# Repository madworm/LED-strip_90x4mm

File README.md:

LED-strip_90.0x3.6mm
=====================

LAYOUT FILES: 90.0mm x 3.6mm LED strip with 9x 0805 LEDs + resistors

---

Before having PC-boards made, please make sure you know about your manufacturer's peculiarities!
Especially drill-sizes and their tolerances may vary too much and give you trouble.

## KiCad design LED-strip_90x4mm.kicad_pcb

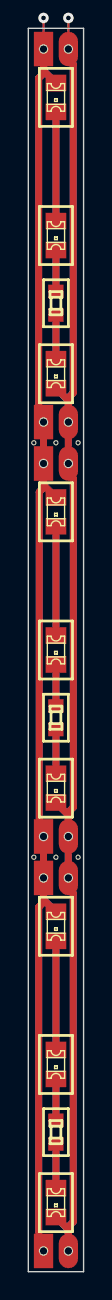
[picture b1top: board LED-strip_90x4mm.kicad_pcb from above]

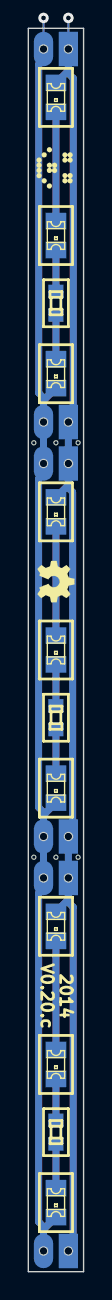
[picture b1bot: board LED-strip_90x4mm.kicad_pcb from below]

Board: 2 copper layers, 4.0 x 90.0 mm, 38 parts (20 on the bottom side), 20 nets.

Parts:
D1, D2, D3, D4, D5, D6, D7, D8, D9, D10, D11, D12, D13, D14, D15, D16, D17, D18: LED; MADW__CHIPLED-0805
G1: LED_smile_silkscreen_3mm
G2: OSHW-logo_silkscreen_3mm
P1, P2, P3, P4, P5, P6, P7, P8, P9, P10, P11, P12: CONN_2; MADW__SMD_2-pin_square_3.2x2.5mm
R1, R2, R3, R4, R5, R6: R; MADW__R0603_2

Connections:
/GND: D3.2, D6.2, D9.2, D12.2, D15.2, D18.2, P1.2, P2.2, P3.2, P4.2, P5.2, P6.2, P7.2, P8.2, P9.2, P10.2, P11.2, P12.2
/VCC: D1.1, D4.1, D7.1, D10.1, D13.1, D16.1, P1.1, P2.1, P3.1, P4.1, P5.1, P6.1, P7.1, P8.1, P9.1, P10.1, P11.1, P12.1
unnamed: D1.2, D2.1
unnamed: D2.2, R1.1
unnamed: D3.1, R1.2
unnamed: D4.2, D5.1
unnamed: D5.2, R2.1
unnamed: D6.1, R2.2
unnamed: D7.2, D8.1
unnamed: D8.2, R3.1
unnamed: D9.1, R3.2
unnamed: D10.2, D11.1
unnamed: D11.2, R4.1
unnamed: D12.1, R4.2
unnamed: D13.2, D14.1
unnamed: D14.2, R5.1
unnamed: D15.1, R5.2
unnamed: D16.2, D17.1
unnamed: D17.2, R6.1
unnamed: D18.1, R6.2

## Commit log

2014-05-18 Added commit-ID to gerber files of the panel (fdf2c798...).
2014-05-19 Changed board-width to 4mm - renamed repo...
2014-05-20 Added slots to board. Might got double-sided-load after all.
    Made with KiCad BZR4865 (later revs. just crash too often).
2014-05-21 Duplicated F_Cu to B_Cu.
2014-05-21 Tweaks.
2014-05-24 Removed internal routing (useless).
2014-05-24 Removed fiducials + alignment holes from panel --> 20% more boards.
2014-05-25 Changed edge-connector footprint.
2014-05-25 Redid the panel.
2014-06-27 Some tweaks (single board for now). Panel later.
